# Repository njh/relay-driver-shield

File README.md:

Relay Driver Shield
===================

An Arduino shield for controlling four 12v relays.
The schematic and PCB layout were created using [KiCad](http://kicad-pcb.org/).

While it is designed for relays, it can be used for powering anything
that requires a bit more current or voltage.

| Arduino Pin | Function  |
|-------------|-----------|
| `D5`        | Relay 1   |
| `D6`        | Relay 2   |
| `D7`        | Relay 3   |
| `D8`        | Relay 4   |

The output voltage is determined by the input voltage on the Arduino Board - the `VIN` pin.

Schematic
---------

PCB Layout
----------

Dependencies
------------

This shield makes use of the [Arduino KiCad Library](https://github.com/Alarm-Siren/arduino-kicad-library)
by [Nicholas Parks Young](https://github.com/alarm-siren).

License
-------

All of the files in this repository are licensed under
[Creative Commons Attribution Share-Alike License 4.0 CC-BY-SA](https://creativecommons.org/licenses/by-sa/4.0/).

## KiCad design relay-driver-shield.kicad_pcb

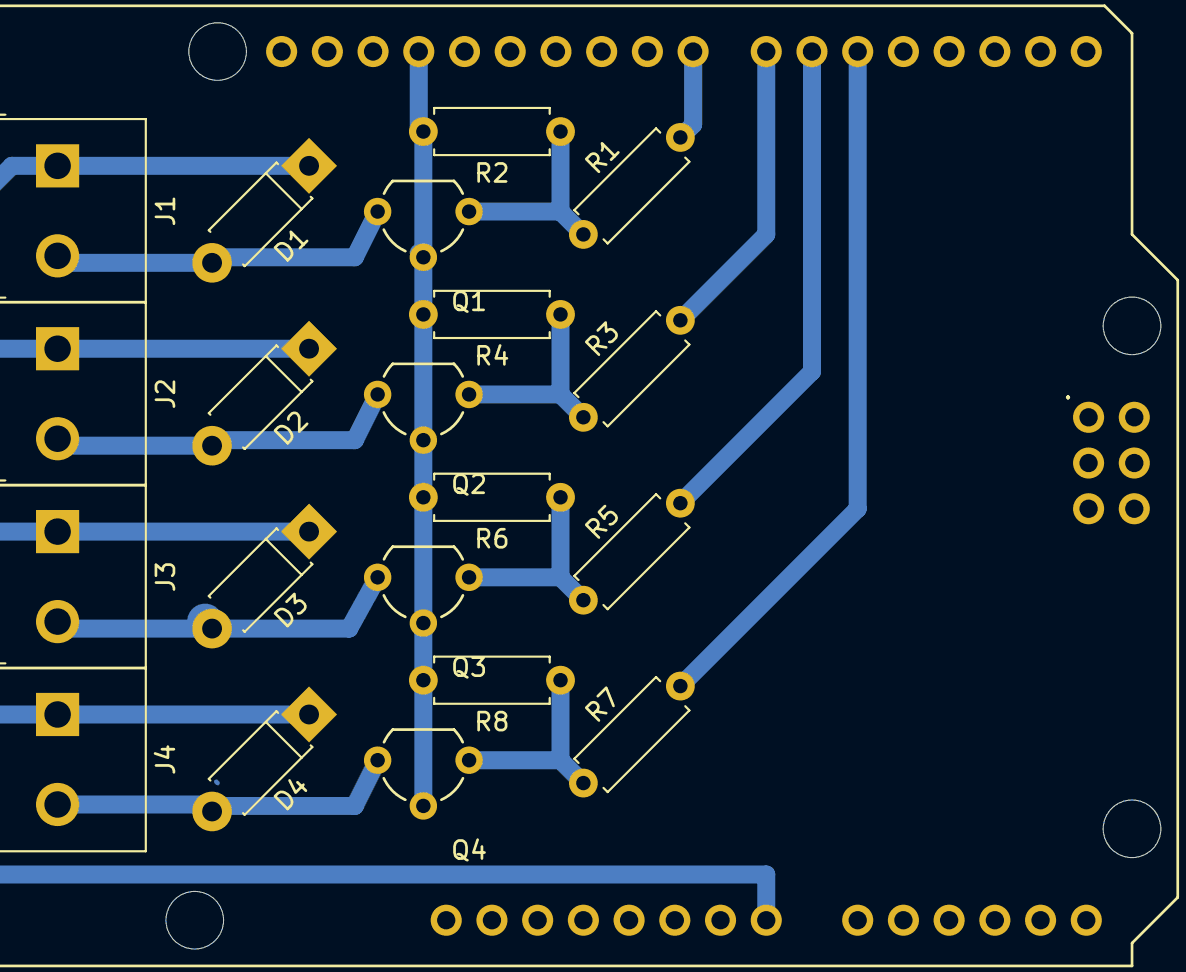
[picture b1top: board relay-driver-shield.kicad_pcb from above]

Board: 2 copper layers, 21 parts (0 on the bottom side), 14 nets.

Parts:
ARD1: Arduino_Uno_Shield
D1, D2, D3, D4: 1N4004; D_DO-41_SOD81_P7.62mm_Horizontal
J1, J2, J3, J4: Screw_Terminal_01x02; TerminalBlock_Philmore_TB132_02x5mm_Straight
Q1, Q2, Q3, Q4: 2N7002; TO-92_Molded_Wide
R1, R3, R5, R7: 1K; R_Axial_DIN0207_L6.3mm_D2.5mm_P7.62mm_Horizontal
R2, R4, R6, R8: 10K; R_Axial_DIN0207_L6.3mm_D2.5mm_P7.62mm_Horizontal

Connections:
+12V: ARD1.VIN, D1.1, D2.1, D3.1, D4.1, J1.1, J2.1, J3.1, J4.1
GND: ARD1.GND1, ARD1.GND2, ARD1.GND3, ARD1.GND4, Q1.2, Q2.2, Q3.2, Q4.2, R2.2, R4.2, R6.2, R8.2
unnamed: ARD1.D5, R7.2
unnamed: ARD1.D6, R5.2
unnamed: ARD1.D7, R3.2
unnamed: ARD1.D8, R1.2
unnamed: D1.2, J1.2, Q1.3
unnamed: D2.2, J2.2, Q2.3
unnamed: D3.2, J3.2, Q3.3
unnamed: D4.2, J4.2, Q4.3
unnamed: Q1.1, R1.1, R2.1
unnamed: Q2.1, R3.1, R4.1
unnamed: Q3.1, R5.1, R6.1
unnamed: Q4.1, R7.1, R8.1

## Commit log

2017-11-23 Added .gitignore for KiCad https://github.com/github/gitignore/blob/master/KiCad.gitignore
2017-11-23 Initial check in of Schematic
2017-11-23 Added Creative Commons Attribution-ShareAlike 4.0 International license
2017-11-25 Switched from 01x08 Screw Terminal to 4x 01x02
2017-11-25 Created PCB layout using pcbnew
2017-11-25 Removed bridge between GND1, GND2 and GND3 Not needed and avoids problems with Electrical Rule Checker
2017-11-26 Added values to the resistors and diodes
2017-11-26 Moved components closer together on PCB
2017-11-27 Added copper fill to bottom
2017-11-27 Added details and screenshots to the README
2017-11-27 Added arduino-kicad-library as a sub-module to the project
2017-11-28 Grammar correction in README
2017-11-28 Updated arduino-kicad-library to v1.1 tag
